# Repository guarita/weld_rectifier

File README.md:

# weld_rectifier
Weld Rectifier Project

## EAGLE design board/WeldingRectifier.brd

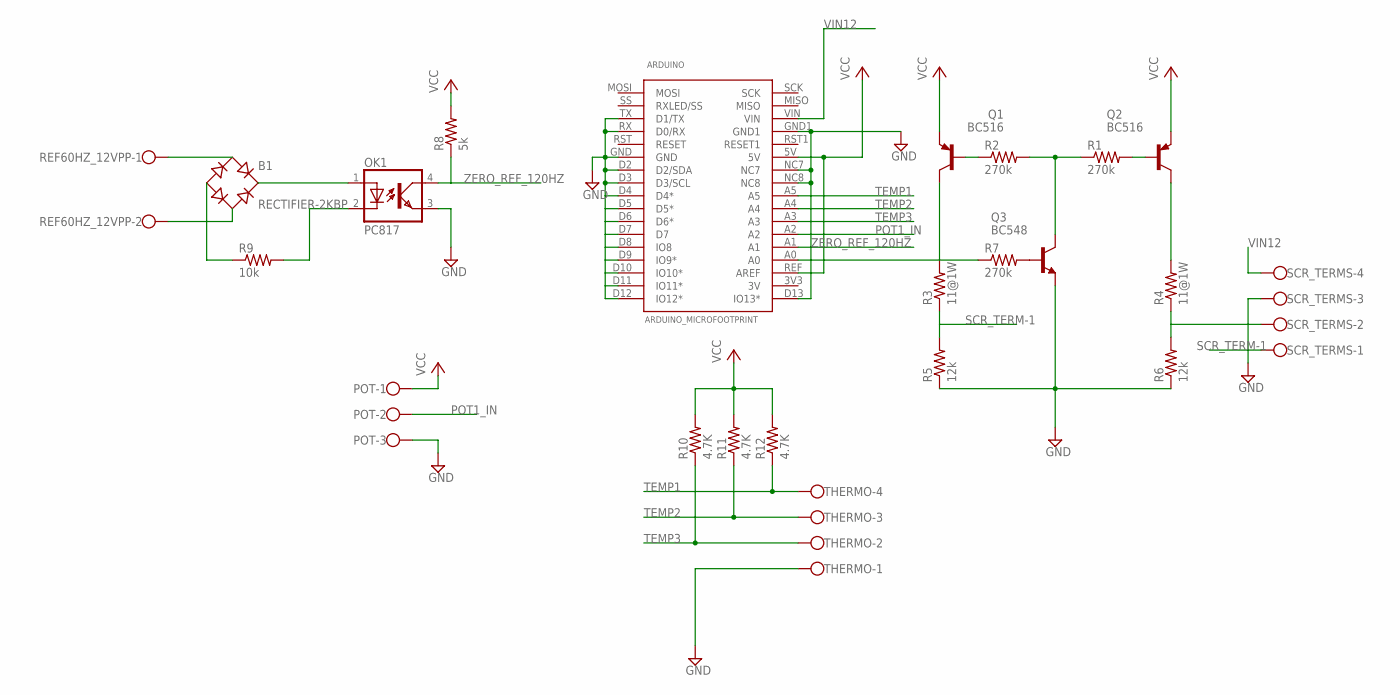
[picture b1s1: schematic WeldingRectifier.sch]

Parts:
ARDUINO: ARDUINO_MICROFOOTPRINT; ARDUINO-MICRO
B1: RECTIFIER-2KBP; 2KBP
OK1: PC817; DIL04
POT: W237-103
Q1, Q2: BC516; TO92-EBC
Q3: BC548; TO92-EBC
R1, R2, R7: 270k; 0204/7
R3, R4: 11@1W; 0204/7
R5, R6: 12k; 0204/7
R8: 5k; 0204/7
R9: 10k; 0204/7
R10, R11, R12: 4.7K; 0204/7
REF60HZ_12VPP: W237-102
SCR_TERMS: W237-4
THERMO: W237-4

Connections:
GND: ARDUINO.D2 (D2/SDA), ARDUINO.D3 (D3/SCL), ARDUINO.D4 (D4*), ARDUINO.D5 (D5*), ARDUINO.D6 (D6*), ARDUINO.D7, ARDUINO.D8 (IO8), ARDUINO.D9 (IO9*), ARDUINO.D10 (IO10*), ARDUINO.D11 (IO11*), ARDUINO.D12 (IO12*), ARDUINO.D13 (IO13*), ARDUINO.GND, ARDUINO.GND1, ARDUINO.NC7, ARDUINO.NC8, ARDUINO.RX (D0/RX), ARDUINO.TX (D1/TX), OK1.3 (EMIT), POT.3, Q3.E, R5.1, R6.1, SCR_TERMS.3, THERMO.1
unnamed: Q1.C, R3.2
unnamed: Q3.B, R7.2
unnamed: B1.-, R9.1
unnamed: R4.1, R6.2, SCR_TERMS.2
unnamed: Q2.C, R4.2
unnamed: Q3.C, R1.1, R2.2
unnamed: Q1.B, R2.1
unnamed: Q2.B, R1.2
unnamed: B1.AC1, REF60HZ_12VPP.1
unnamed: B1.AC2, REF60HZ_12VPP.2
unnamed: B1.+, OK1.1 (A)
unnamed: OK1.2 (C), R9.2
POT1_IN: ARDUINO.A2, POT.2
SCR_CTRL: ARDUINO.A0, R7.1
SCR_TERM-1: R3.1, R5.2, SCR_TERMS.1
TEMP1: ARDUINO.A5, R12.1, THERMO.4
TEMP2: ARDUINO.A4, R11.1, THERMO.3
TEMP3: ARDUINO.A3, R10.1, THERMO.2
VCC: ARDUINO.5V, ARDUINO.REF (AREF), POT.1, Q1.E, Q2.E, R8.2, R10.2, R11.2, R12.2
VIN12: ARDUINO.VIN, SCR_TERMS.4
ZERO_REF_120HZ: ARDUINO.A1, OK1.4 (COL), R8.1

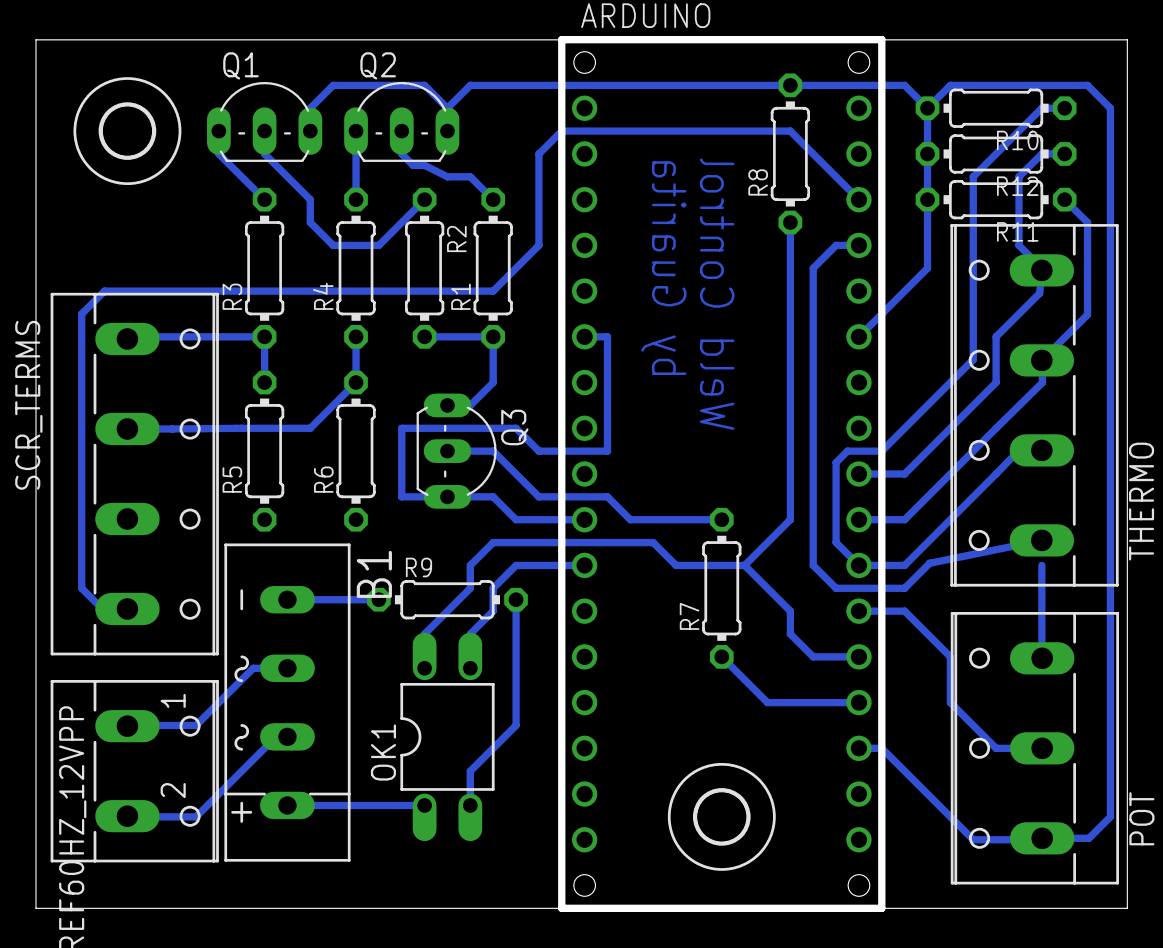
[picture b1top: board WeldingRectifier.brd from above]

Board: 2 copper layers, 60.2 x 48.3 mm, 24 parts (0 on the bottom side), 22 nets.

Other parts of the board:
U$1, U$3: 2,8

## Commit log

2018-08-01 Added eagle files to project
